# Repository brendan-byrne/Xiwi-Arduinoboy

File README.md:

## Arduinoboy - Xiwi Electronics ##

Product Page - <a href="http://xiwielectronics.com/products/arduinoboy">http://tiny.cc/gdzcbx</a><br />
Arduinoboy Google Code Page -  <a href="tiny.cc/bkz4xw">tiny.cc/bkz4xw</a>

Based on the Arduino platform, this device allows for MIDI signals to be sent and received by software such as Nanoloop, LSDJ, and mGB running on the Nintendo Gameboy.

Arduinoboy was developed and released under the GNU General Public License by Timothy Lamb in fall of 2008.

=======
Arduinoboy was developed and released under the GNU General Public License by Timothy Lamb in 2008.

# Files #
**Arduinoboy Code** : Contains the original AB code written by Timothy Lamb. Upload/access via Arduino<br />

**Eagle Files** : Contains Eagle PCB and Schematic files for Xiwi Electronics Arduinoboy.<br />

**AB Editor - MIDI** : Max/MSP patch for altering MIDI channel information on the Arduinoboy. Requires MIDI In and Out ports on Arduinoboy.

**AB Enclosure** : Contains Adobe Illustrator vector drawing of Arduinoboy enclosure. Use file with laser cutter to fabricate enclosure.

**Arduino Boy Kit Assembly Instructions** : Instructions for assembling the kit sold through Xiwi Electronics. <a href="http://xiwielectronics.com/products/arduinoboy-kit">http://tiny.cc/5bzcbx</a>

**Bill of Materials** : All components and hardware used in construction of Xiwi Arduinoboy. Contains product numbers mostly through Mouser.

**Operational Document** : Layout of Xiwi Arduinoboy operations.

**mGB1_3_0.gb** : ROM file for mGB. Upload to Gameboy flash cartridge. Can receive MIDI note information to access Gameboy's internal synthesis chips. More documentation on Google Code page.

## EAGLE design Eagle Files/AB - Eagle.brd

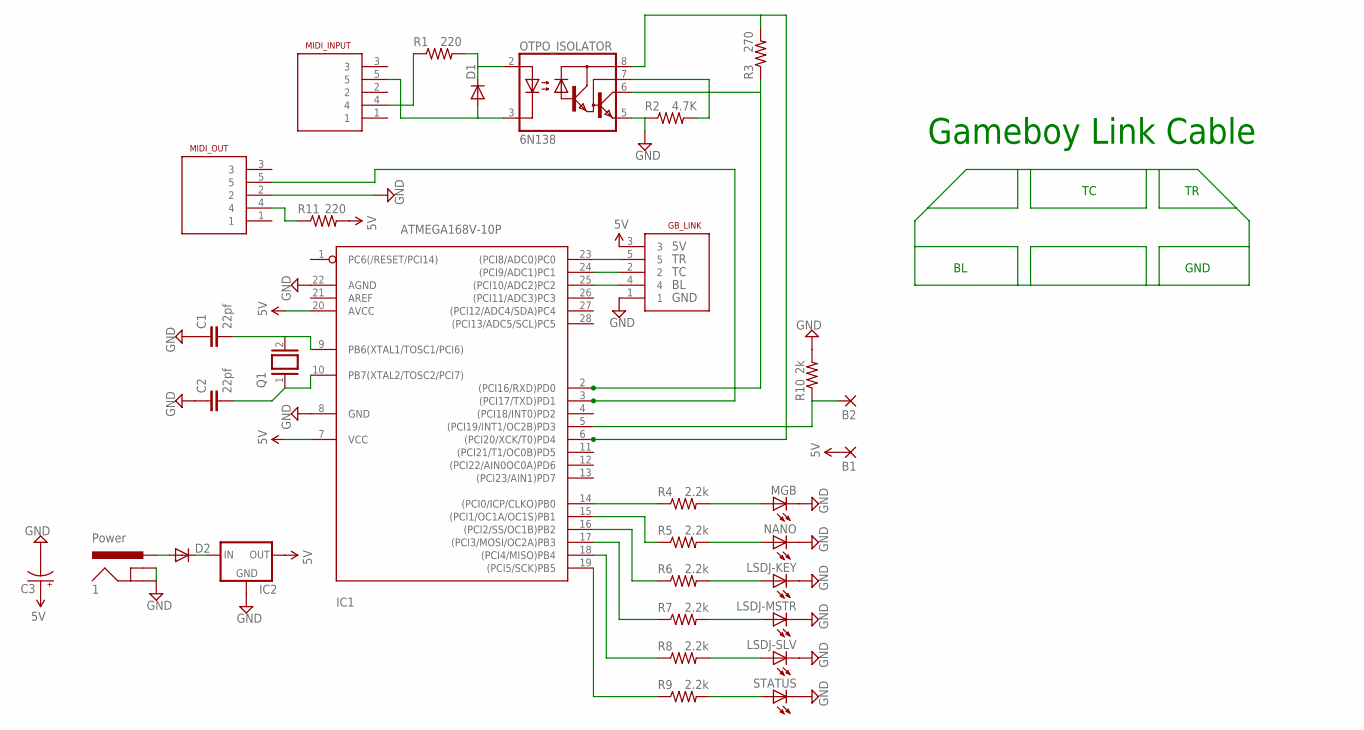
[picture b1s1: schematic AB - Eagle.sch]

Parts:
1: Power; POWER_JACK_PTH
B1, B2: 2,15/1,0
C1, C2: 22pf; CAP-PTH-SMALL2
C3: CAP_POLPTH2; CPOL-RADIAL-10UF-25V
D1, D2: DIODE1N4148; DIODE-1N4148
GB_LINK: MIDI_CONN_FEMALE_SUPPORT; DIN_5_FEMALE_SUPPORT
IC1: ATMEGA168V-10P; DIL28-3
IC2: V_REG_78XX-TO-220; TO-220-ALT
LSDJ-KEY: LED3MM
LSDJ-MSTR: LED3MM
LSDJ-SLV: LED3MM
MGB: LED3MM
MIDI_INPUT: MIDI_CONN_FEMALE_SUPPORT; DIN_5_FEMALE_SUPPORT
MIDI_OUT: MIDI_CONN_FEMALE_SUPPORT; DIN_5_FEMALE_SUPPORT
NANO: LED3MM
OTPO_ISOLATOR: 6N138; DIL08
Q1: XTAL/S; QS
R1, R11: 220; AXIAL-0.3
R2: 4.7K; AXIAL-0.3
R3: 270; AXIAL-0.3
R4, R5, R6, R7, R8, R9: 2.2k; AXIAL-0.3
R10: 2k; AXIAL-0.3
STATUS: LED3MM

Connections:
5V: B1.1, C3.1 (+), GB_LINK.3, IC1.7 (VCC), IC1.20 (AVCC), IC2.OUT, R11.P$2 (2)
GND: 1.GND, 1.GNDBREAK, C1.1, C2.1, C3.2 (-), GB_LINK.1, IC1.8 (GND), IC1.22 (AGND), IC2.GND, LSDJ-KEY.K (C), LSDJ-MSTR.K (C), LSDJ-SLV.K (C), MGB.K (C), MIDI_OUT.2, NANO.K (C), OTPO_ISOLATOR.5 (GND), R2.P$1 (1), R10.P$2 (2), STATUS.K (C)
unnamed: D1.C, OTPO_ISOLATOR.2 (A), R1.P$2 (2)
unnamed: IC1.14 ((PCI0/ICP/CLKO)PB0), R4.P$1 (1)
unnamed: GB_LINK.5, IC1.23 ((PCI8/ADC0)PC0)
unnamed: B2.1, IC1.5 ((PCI19/INT1/OC2B)PD3), R10.P$1 (1)
unnamed: IC1.15 ((PCI1/OC1A/OC1S)PB1), R5.P$1 (1)
unnamed: IC1.16 ((PCI2/SS/OC1B)PB2), R6.P$1 (1)
unnamed: IC1.17 ((PCI3/MOSI/OC2A)PB3), R7.P$1 (1)
unnamed: IC1.18 ((PCI4/MISO)PB4), R8.P$1 (1)
unnamed: OTPO_ISOLATOR.7 (VB), R2.P$2 (2)
unnamed: IC1.19 ((PCI5/SCK)PB5), R9.P$1 (1)
unnamed: IC1.2 ((PCI16/RXD)PD0), OTPO_ISOLATOR.6 (VO), R3.P$1 (1)
unnamed: MGB.A, R4.P$2 (2)
unnamed: NANO.A, R5.P$2 (2)
unnamed: LSDJ-KEY.A, R6.P$2 (2)
unnamed: LSDJ-MSTR.A, R7.P$2 (2)
unnamed: LSDJ-SLV.A, R8.P$2 (2)
unnamed: R9.P$2 (2), STATUS.A
unnamed: C2.2, IC1.10 (PB7(XTAL2/TOSC2/PCI7)), Q1.1
unnamed: C1.2, IC1.9 (PB6(XTAL1/TOSC1/PCI6)), Q1.2
unnamed: GB_LINK.2, IC1.24 ((PCI9/ADC1)PC1)
unnamed: GB_LINK.4, IC1.25 ((PCI10/ADC2)PC2)
unnamed: 1.PWR, D2.A
unnamed: D2.C, IC2.IN
unnamed: MIDI_INPUT.4, R1.P$1 (1)
unnamed: D1.A, MIDI_INPUT.5, OTPO_ISOLATOR.3 (C)
unnamed: MIDI_OUT.4, R11.P$1 (1)
unnamed: IC1.6 ((PCI20/XCK/T0)PD4), OTPO_ISOLATOR.8 (VCC), R3.P$2 (2)
TXOUT: IC1.3 ((PCI17/TXD)PD1), MIDI_OUT.5

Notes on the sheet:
GND
Gameboy Link Cable

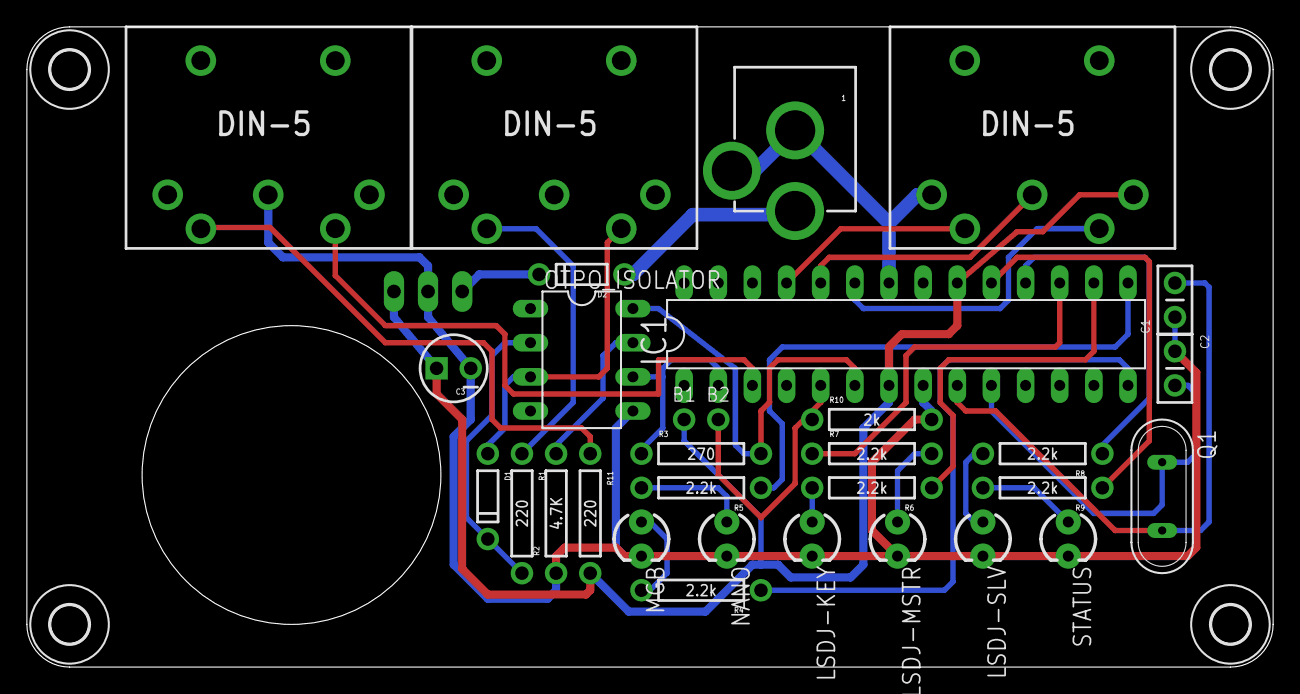
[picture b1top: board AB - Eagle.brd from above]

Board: 2 copper layers, 92.7 x 47.6 mm, 36 parts (0 on the bottom side), 30 nets.

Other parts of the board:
U$2, U$3, U$4, U$5: 2,8

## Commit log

2014-02-16 $ git commit
2014-05-02 new photo
    new photo
2014-07-04 lsdj ab

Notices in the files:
parts and their libraries:
SparkFun-DiscreteSemi: Licensing: CC v3.0 Share-Alike You are welcome to use this library for commercial purposes.
